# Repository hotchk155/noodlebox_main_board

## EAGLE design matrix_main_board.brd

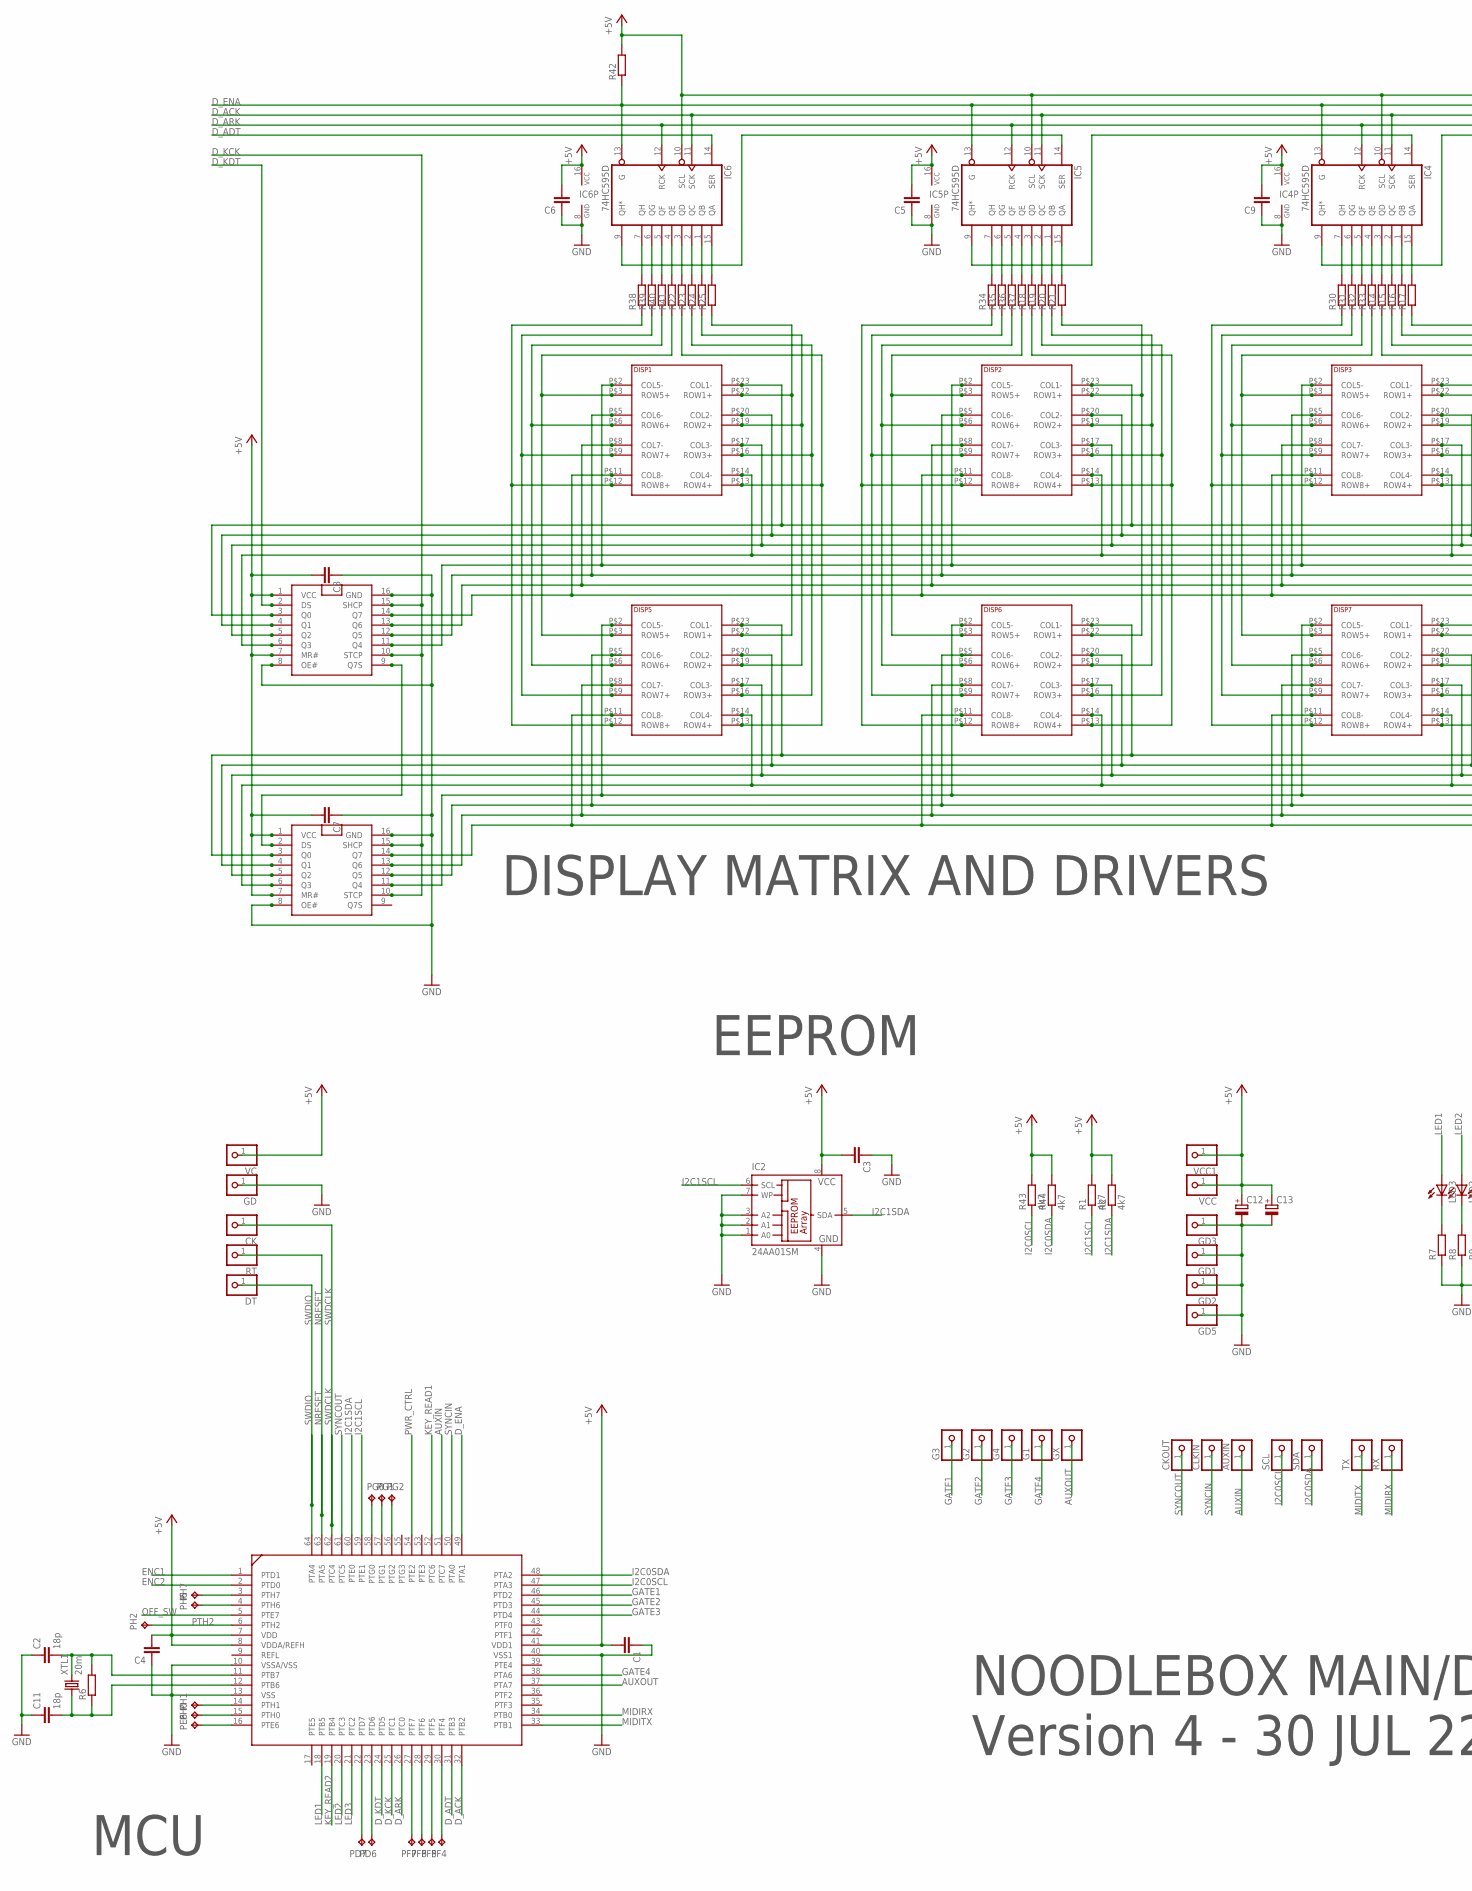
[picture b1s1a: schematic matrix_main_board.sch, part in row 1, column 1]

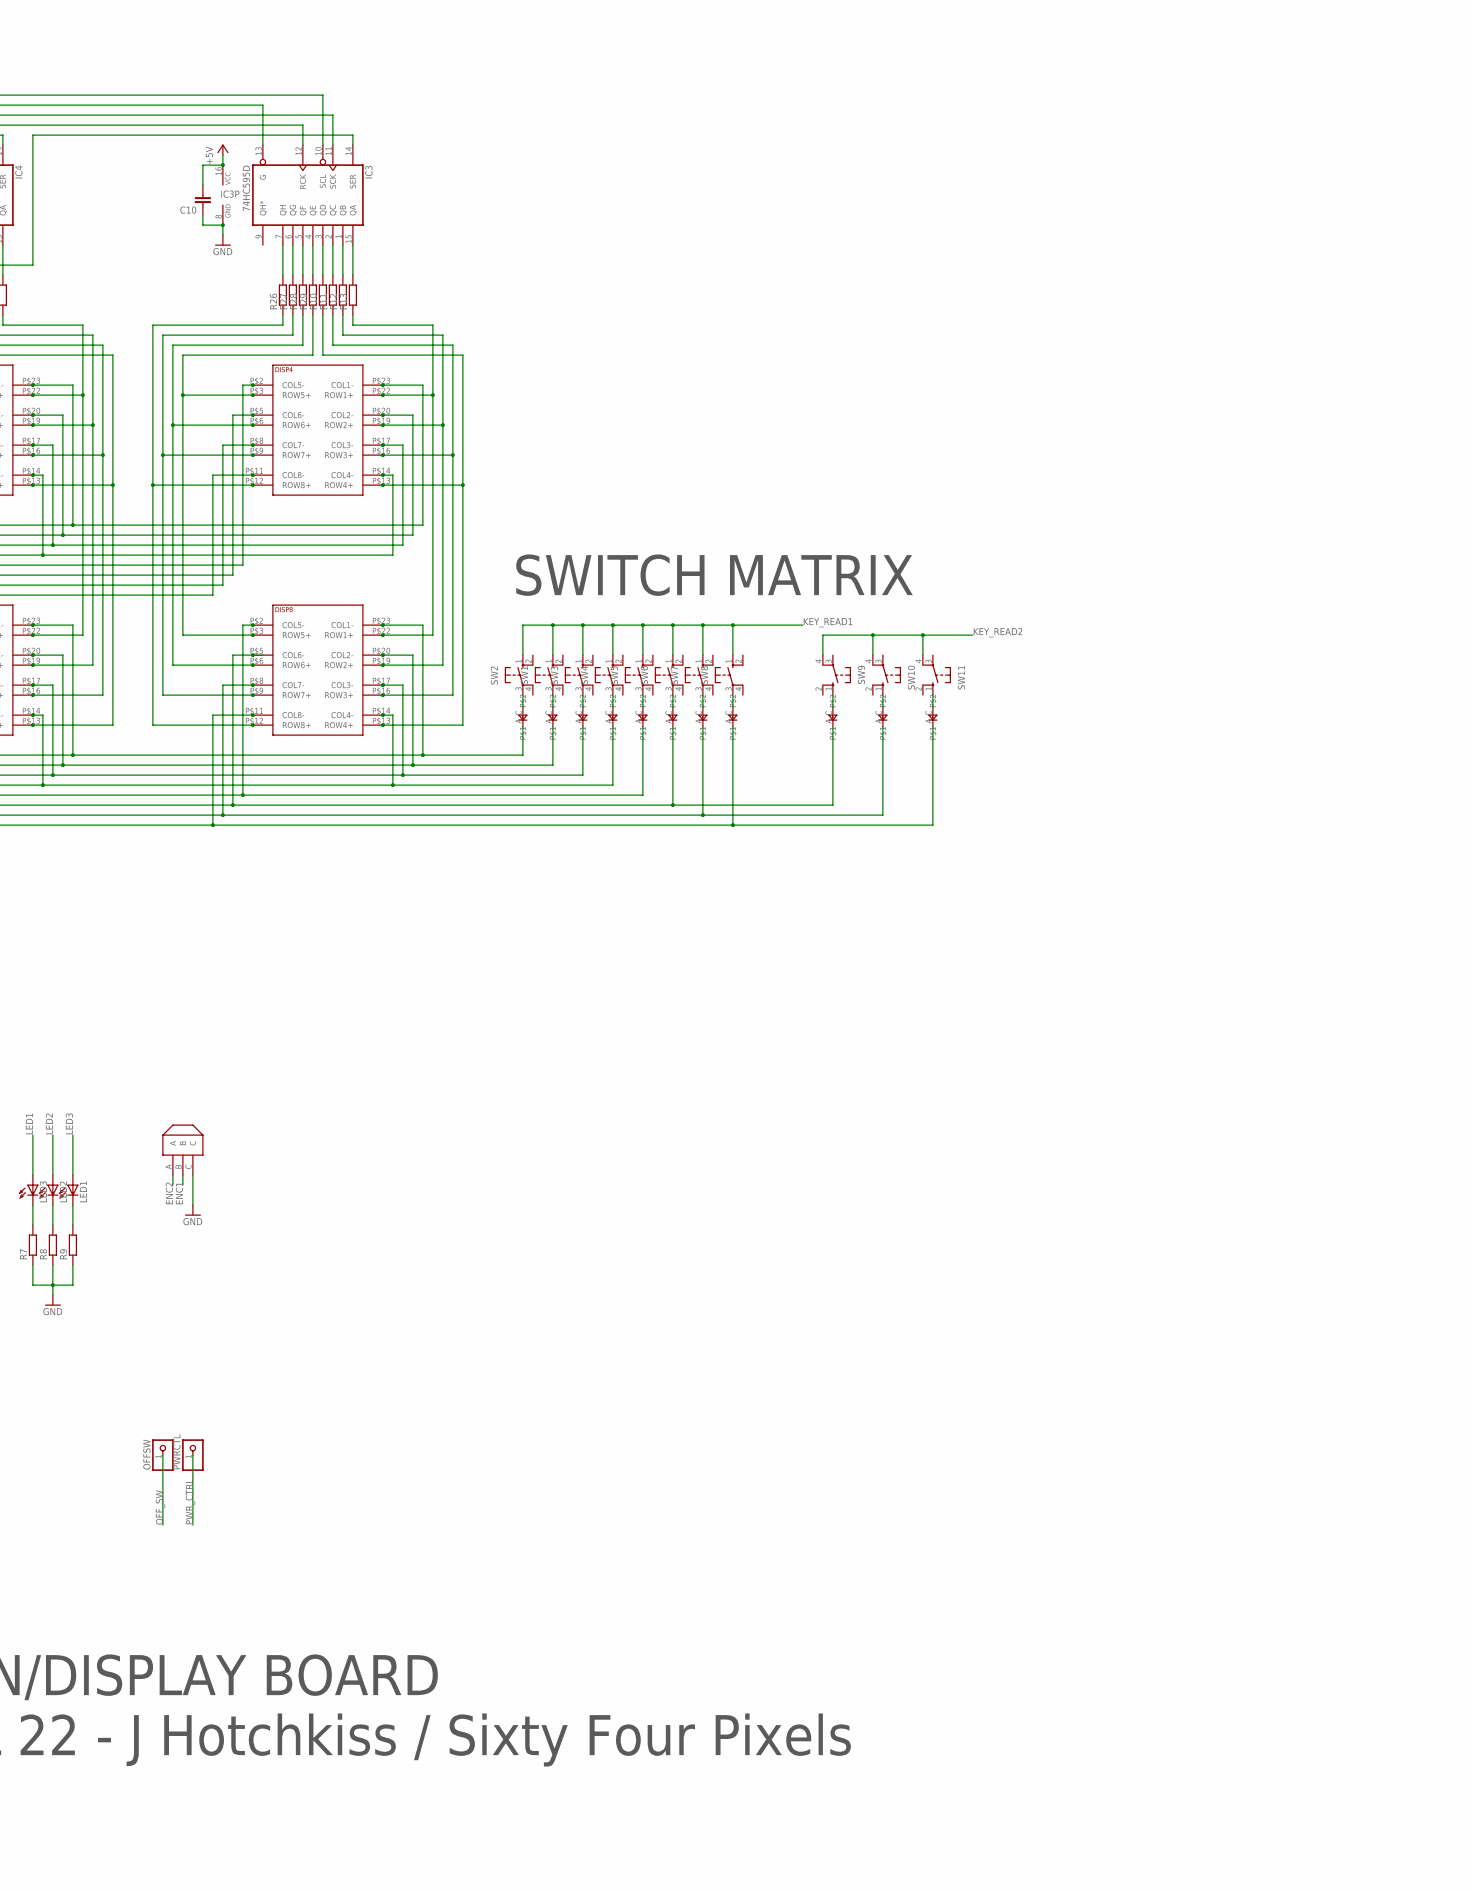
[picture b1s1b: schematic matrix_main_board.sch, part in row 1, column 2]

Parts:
AUXIN: PINHD-1X1; 1X01
C1, C3, C4, C5, C6, C7, C8, C9, C10: C-EUC0805; C0805
C2, C11: 18p; C0805
C12, C13: CPOL-EUE2.5-7; E2,5-7
CK: PINHD-1X1; 1X01
CKOUT: PINHD-1X1; 1X01
CLKIN: PINHD-1X1; 1X01
D1, D2, D3, D4, D5, D6, D7, D8, D9, D10, D11: 0805DIODE
DISP1, DISP2, DISP3, DISP4, DISP5, DISP6, DISP7, DISP8: 1388BBMATRIX24PIN; 1388_24PIN
DT: PINHD-1X1; 1X01
ENC1: ENCODER
G1, G2, G3, G4: PINHD-1X1; 1X01
GD, GD1, GD2, GD3, GD5: PINHD-1X1; 1X01
GX: PINHD-1X1; 1X01
IC1: MKE02_64PINQFP64; QFP64_SOT393
IC2: 24AA01SM; SO-08M
IC3, IC4, IC5, IC6: 74HC595D; SO16
IC7, IC8: NPIC6C596; SO16
LED1, LED2, LED3: LED3MM
OFFSW: PINHD-1X1; 1X01
PD6, PD7: TPTP17R; TP17R
PE6: TPTP17R; TP17R
PF4, PF5, PF6, PF7: TPTP17R; TP17R
PG0, PG1, PG2: TPTP17R; TP17R
PH0, PH1, PH2, PH6, PH7: TPTP17R; TP17R
PWRCTL: PINHD-1X1; 1X01
R1, R2, R43, R44: 4k7; R0805
R6, R7, R8, R9, R10, R11, R12, R13, R14, R15, R16, R17, R18, R19, R20, R21, R22, R23, R24, R25, R26, R27, R28, R29, R30, R31, R32, R33, R34, R35, R36, R37, R38, R39, R40, R41, R42: R-EU_R0805; R0805
RT: PINHD-1X1; 1X01
RX: PINHD-1X1; 1X01
SCL: PINHD-1X1; 1X01
SDA: PINHD-1X1; 1X01
SW1, SW2, SW3, SW4, SW5, SW6, SW7, SW8: 40-XX; B3F-40XX
SW9, SW10, SW11: 10-XX; B3F-10XX
TX: PINHD-1X1; 1X01
VC: PINHD-1X1; 1X01
VCC, VCC1: PINHD-1X1; 1X01
XTL1: 20m; HC49/S

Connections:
+5V: C1.2, C3.2, C4.2, C5.2, C6.2, C7.2, C8.2, C9.2, C10.2, C12.+, C13.+, IC1.7 (VDD), IC1.8 (VDDA/REFH), IC1.41 (VDD1), IC2.8 (VCC), IC3.10 (SCL), IC3.16 (VCC), IC4.10 (SCL), IC4.16 (VCC), IC5.10 (SCL), IC5.16 (VCC), IC6.10 (SCL), IC6.16 (VCC), IC7.1 (VCC), IC7.7 (MR#), IC8.1 (VCC), IC8.7 (MR#), R1.2, R2.2, R42.2, R43.2, R44.2, VC.1, VCC.1, VCC1.1
A0: DISP1.P$22 (ROW1+), DISP5.P$22 (ROW1+), R25.1
A1: DISP1.P$19 (ROW2+), DISP5.P$19 (ROW2+), R24.1
A2: DISP1.P$16 (ROW3+), DISP5.P$16 (ROW3+), R23.1
A3: DISP1.P$13 (ROW4+), DISP5.P$13 (ROW4+), R22.1
A4: DISP1.P$3 (ROW5+), DISP5.P$3 (ROW5+), R41.1
A5: DISP1.P$6 (ROW6+), DISP5.P$6 (ROW6+), R40.1
A6: DISP1.P$9 (ROW7+), DISP5.P$9 (ROW7+), R39.1
A7: DISP1.P$12 (ROW8+), DISP5.P$12 (ROW8+), R38.1
A8: DISP2.P$22 (ROW1+), DISP6.P$22 (ROW1+), R21.1
A9: DISP2.P$19 (ROW2+), DISP6.P$19 (ROW2+), R20.1
A10: DISP2.P$16 (ROW3+), DISP6.P$16 (ROW3+), R19.1
A11: DISP2.P$13 (ROW4+), DISP6.P$13 (ROW4+), R18.1
A12: DISP2.P$3 (ROW5+), DISP6.P$3 (ROW5+), R37.1
A13: DISP2.P$6 (ROW6+), DISP6.P$6 (ROW6+), R36.1
A14: DISP2.P$9 (ROW7+), DISP6.P$9 (ROW7+), R35.1
A15: DISP2.P$12 (ROW8+), DISP6.P$12 (ROW8+), R34.1
A16: DISP3.P$22 (ROW1+), DISP7.P$22 (ROW1+), R17.1
A17: DISP3.P$19 (ROW2+), DISP7.P$19 (ROW2+), R16.1
A18: DISP3.P$16 (ROW3+), DISP7.P$16 (ROW3+), R15.1
A19: DISP3.P$13 (ROW4+), DISP7.P$13 (ROW4+), R14.1
A20: DISP3.P$3 (ROW5+), DISP7.P$3 (ROW5+), R33.1
A21: DISP3.P$6 (ROW6+), DISP7.P$6 (ROW6+), R32.1
A22: DISP3.P$9 (ROW7+), DISP7.P$9 (ROW7+), R31.1
A23: DISP3.P$12 (ROW8+), DISP7.P$12 (ROW8+), R30.1
A24: DISP4.P$22 (ROW1+), DISP8.P$22 (ROW1+), R13.1
A25: DISP4.P$19 (ROW2+), DISP8.P$19 (ROW2+), R12.1
A26: DISP4.P$16 (ROW3+), DISP8.P$16 (ROW3+), R11.1
A27: DISP4.P$13 (ROW4+), DISP8.P$13 (ROW4+), R10.1
A28: DISP4.P$3 (ROW5+), DISP8.P$3 (ROW5+), R29.1
A29: DISP4.P$6 (ROW6+), DISP8.P$6 (ROW6+), R28.1
A30: DISP4.P$9 (ROW7+), DISP8.P$9 (ROW7+), R27.1
A31: DISP4.P$12 (ROW8+), DISP8.P$12 (ROW8+), R26.1
AUXIN: AUXIN.1, IC1.51 (PTC7)
AUXOUT: GX.1, IC1.37 (PTA7)
D_ACK: IC1.32 (PTB2), IC3.11 (SCK), IC4.11 (SCK), IC5.11 (SCK), IC6.11 (SCK)
D_ADT: IC1.31 (PTB3), IC6.14 (SER)
D_ARK: IC1.26 (PTC0), IC3.12 (RCK), IC4.12 (RCK), IC5.12 (RCK), IC6.12 (RCK)
D_ENA: IC1.49 (PTA1), IC3.13 (G), IC4.13 (G), IC5.13 (G), IC6.13 (G), R42.1
D_KCK: IC1.25 (PTC1), IC7.10 (STCP), IC7.15 (SHCP), IC8.10 (STCP), IC8.15 (SHCP)
D_KDT: IC1.24 (PTD5), IC8.2 (DS)
ENC1: ENC1.B, IC1.1 (PTD1)
ENC2: ENC1.A, IC1.2 (PTD0)
GATE1: G3.1, IC1.46 (PTD2)
GATE2: G2.1, IC1.45 (PTD3)
GATE3: G4.1, IC1.44 (PTD4)
GATE4: G1.1, IC1.38 (PTA6)
GND: C1.1, C2.1, C3.1, C4.1, C5.1, C6.1, C7.1, C8.1, C9.1, C10.1, C11.1, C12.-, C13.-, ENC1.C, GD.1, GD1.1, GD2.1, GD3.1, GD5.1, IC1.10 (VSSA/VSS), IC1.13 (VSS), IC1.40 (VSS1), IC2.1 (A0), IC2.2 (A1), IC2.3 (A2), IC2.4 (GND), IC2.7 (WP), IC3.8 (GND), IC4.8 (GND), IC5.8 (GND), IC6.8 (GND), IC7.8 (OE#), IC7.16 (GND), IC8.8 (OE#), IC8.16 (GND), R7.1, R8.1, R9.1
I2C0SCL: IC1.47 (PTA3), R43.1, SCL.1
I2C0SDA: IC1.48 (PTA2), R44.1, SDA.1
I2C1SCL: IC1.59 (PTE1), IC2.6 (SCL), R1.1
I2C1SDA: IC1.60 (PTE0), IC2.5 (SDA), R2.1
K0: DISP1.P$23 (COL1-), DISP2.P$23 (COL1-), DISP3.P$23 (COL1-), DISP4.P$23 (COL1-), IC8.3 (Q0)
K1: DISP1.P$20 (COL2-), DISP2.P$20 (COL2-), DISP3.P$20 (COL2-), DISP4.P$20 (COL2-), IC8.4 (Q1)
K2: DISP1.P$17 (COL3-), DISP2.P$17 (COL3-), DISP3.P$17 (COL3-), DISP4.P$17 (COL3-), IC8.5 (Q2)
K3: DISP1.P$14 (COL4-), DISP2.P$14 (COL4-), DISP3.P$14 (COL4-), DISP4.P$14 (COL4-), IC8.6 (Q3)
K4: DISP1.P$2 (COL5-), DISP2.P$2 (COL5-), DISP3.P$2 (COL5-), DISP4.P$2 (COL5-), IC8.11 (Q4)
K5: DISP1.P$5 (COL6-), DISP2.P$5 (COL6-), DISP3.P$5 (COL6-), DISP4.P$5 (COL6-), IC8.12 (Q5)
K6: DISP1.P$8 (COL7-), DISP2.P$8 (COL7-), DISP3.P$8 (COL7-), DISP4.P$8 (COL7-), IC8.13 (Q6)
K7: DISP1.P$11 (COL8-), DISP2.P$11 (COL8-), DISP3.P$11 (COL8-), DISP4.P$11 (COL8-), IC8.14 (Q7)
K8: D7.A, DISP5.P$23 (COL1-), DISP6.P$23 (COL1-), DISP7.P$23 (COL1-), DISP8.P$23 (COL1-), IC7.3 (Q0)
K9: D8.A, DISP5.P$20 (COL2-), DISP6.P$20 (COL2-), DISP7.P$20 (COL2-), DISP8.P$20 (COL2-), IC7.4 (Q1)
K10: D6.A, DISP5.P$17 (COL3-), DISP6.P$17 (COL3-), DISP7.P$17 (COL3-), DISP8.P$17 (COL3-), IC7.5 (Q2)
K11: D5.A, DISP5.P$14 (COL4-), DISP6.P$14 (COL4-), DISP7.P$14 (COL4-), DISP8.P$14 (COL4-), IC7.6 (Q3)
K12: D4.A, DISP5.P$2 (COL5-), DISP6.P$2 (COL5-), DISP7.P$2 (COL5-), DISP8.P$2 (COL5-), IC7.11 (Q4)
K13: D3.A, D11.A, DISP5.P$5 (COL6-), DISP6.P$5 (COL6-), DISP7.P$5 (COL6-), DISP8.P$5 (COL6-), IC7.12 (Q5)
K14: D2.A, D10.A, DISP5.P$8 (COL7-), DISP6.P$8 (COL7-), DISP7.P$8 (COL7-), DISP8.P$8 (COL7-), IC7.13 (Q6)
K15: D1.A, D9.A, DISP5.P$11 (COL8-), DISP6.P$11 (COL8-), DISP7.P$11 (COL8-), DISP8.P$11 (COL8-), IC7.14 (Q7)
KEY_READ1: IC1.52 (PTC6), SW1.1 (S), SW2.1 (S), SW3.1 (S), SW4.1 (S), SW5.1 (S), SW6.1 (S), SW7.1 (S), SW8.1 (S)
KEY_READ2: IC1.19 (PTB4), SW9.4 (P1), SW10.4 (P1), SW11.4 (P1)
LED1: IC1.18 (PTB5), LED3.A
LED2: IC1.20 (PTC3), LED2.A
LED3: IC1.21 (PTC2), LED1.A
MIDIRX: IC1.34 (PTB0), RX.1
MIDITX: IC1.33 (PTB1), TX.1
unnamed: D10.C, SW10.1 (S)
unnamed: LED3.K (C), R7.2
unnamed: LED2.K (C), R8.2
unnamed: C2.2, IC1.11 (PTB7), R6.2, XTL1.2
unnamed: C11.2, IC1.12 (PTB6), R6.1, XTL1.1
unnamed: LED1.K (C), R9.2
unnamed: D9.C, SW11.1 (S)
unnamed: D11.C, SW9.1 (S)
unnamed: D7.C, SW2.3
unnamed: IC1.22 (PTD7), PD7.TP
unnamed: D8.C, SW1.3
unnamed: IC1.23 (PTD6), PD6.TP
unnamed: D6.C, SW3.3
unnamed: D5.C, SW4.3
unnamed: IC1.27 (PTF7), PF7.TP
unnamed: D4.C, SW5.3
unnamed: IC6.15 (QA), R25.2
unnamed: IC6.1 (QB), R24.2
unnamed: IC6.2 (QC), R23.2
unnamed: IC6.3 (QD), R22.2
unnamed: IC6.4 (QE), R41.2
unnamed: IC6.5 (QF), R40.2
unnamed: IC6.6 (QG), R39.2
unnamed: IC6.7 (QH), R38.2
unnamed: IC1.28 (PTF6), PF6.TP
unnamed: IC1.29 (PTF5), PF5.TP
unnamed: IC1.30 (PTF4), PF4.TP
unnamed: IC5.14 (SER), IC6.9 (QH*)
unnamed: IC4.14 (SER), IC5.9 (QH*)
unnamed: IC3.14 (SER), IC4.9 (QH*)
unnamed: IC1.14 (PTH1), PH1.TP
unnamed: IC1.15 (PTH0), PH0.TP
unnamed: IC1.16 (PTE6), PE6.TP
unnamed: IC1.4 (PTH6), PH6.TP
unnamed: IC1.57 (PTG1), PG1.TP
unnamed: IC5.15 (QA), R21.2
unnamed: IC5.1 (QB), R20.2
unnamed: IC5.2 (QC), R19.2
unnamed: IC5.3 (QD), R18.2
unnamed: IC5.4 (QE), R37.2
unnamed: IC5.5 (QF), R36.2
unnamed: IC5.6 (QG), R35.2
unnamed: IC5.7 (QH), R34.2
unnamed: D3.C, SW6.3
unnamed: D2.C, SW7.3
unnamed: D1.C, SW8.3
unnamed: IC4.15 (QA), R17.2
unnamed: IC4.1 (QB), R16.2
unnamed: IC4.2 (QC), R15.2
unnamed: IC4.3 (QD), R14.2
unnamed: IC4.4 (QE), R33.2
unnamed: IC4.5 (QF), R32.2
unnamed: IC4.6 (QG), R31.2
unnamed: IC4.7 (QH), R30.2
unnamed: IC3.15 (QA), R13.2
unnamed: IC3.1 (QB), R12.2
unnamed: IC3.2 (QC), R11.2
unnamed: IC3.3 (QD), R10.2
unnamed: IC3.4 (QE), R29.2
unnamed: IC3.5 (QF), R28.2
unnamed: IC3.6 (QG), R27.2
unnamed: IC3.7 (QH), R26.2
unnamed: IC7.2 (DS), IC8.9 (Q7S)
NRESET: IC1.63 (PTA5), RT.1
OFF_SW: IC1.5 (PTE7), OFFSW.1
PG0: IC1.58 (PTG0), PG0.TP
PTG2: IC1.56 (PTG2), PG2.TP
PTH2: IC1.6 (PTH2), PH2.TP
PTH7: IC1.3 (PTH7), PH7.TP
PWR_CTRL: IC1.54 (PTE2), PWRCTL.1
SWDCLK: CK.1, IC1.62 (PTC4)
SWDIO: DT.1, IC1.64 (PTA4)
SYNCIN: CLKIN.1, IC1.50 (PTA0)
SYNCOUT: CKOUT.1, IC1.61 (PTC5)

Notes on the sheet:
DISPLAY MATRIX AND DRIVERS
SWITCH MATRIX
MCU
EEPROM
NOODLEBOX MAIN/DISPLAY BOARD
Version 4 - 30 JUL 22 - J Hotchkiss / Sixty Four Pixels

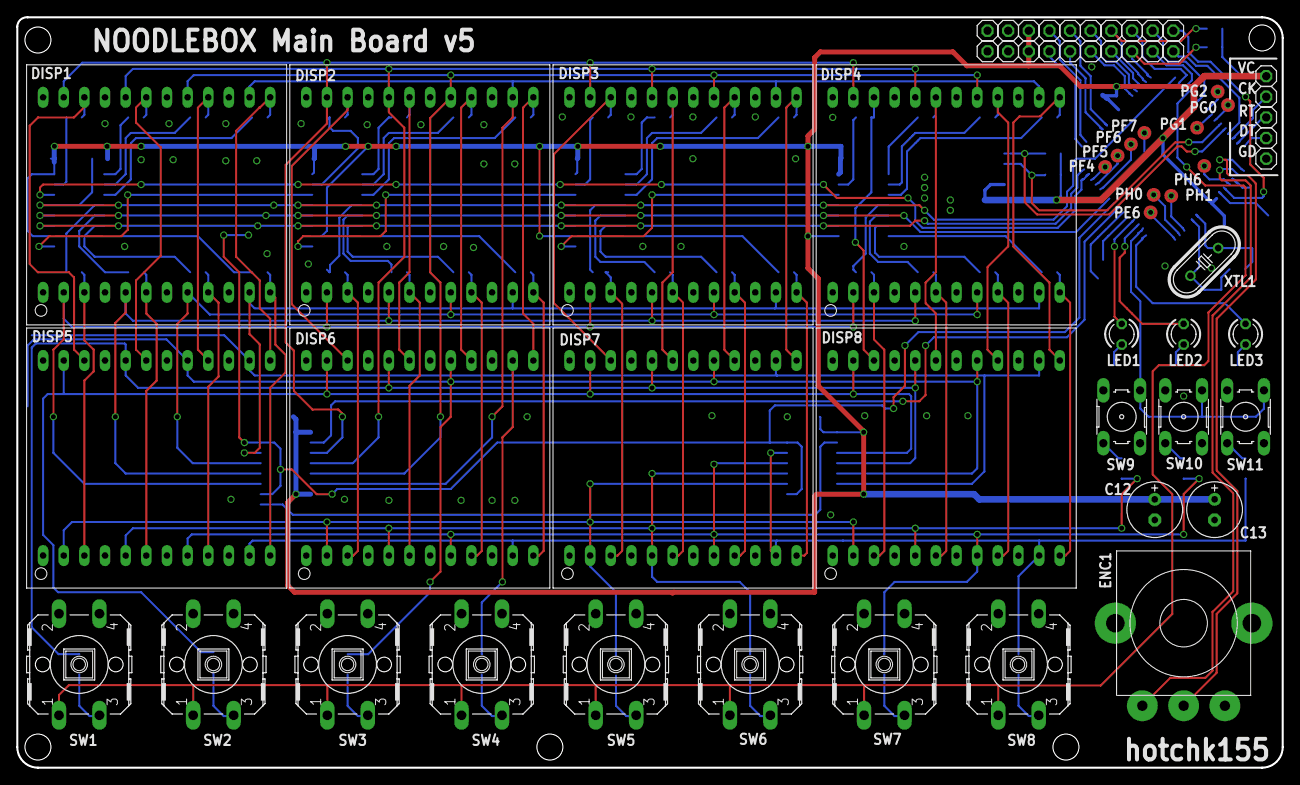
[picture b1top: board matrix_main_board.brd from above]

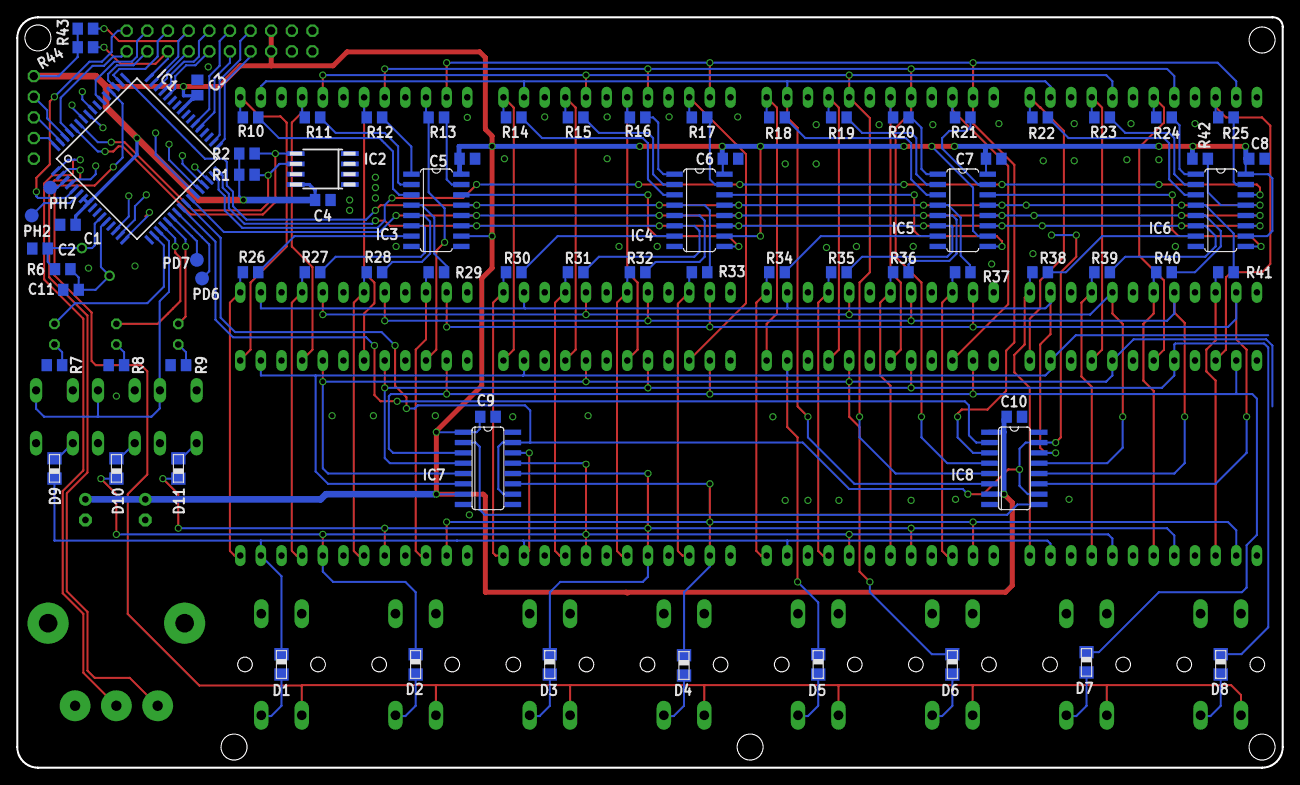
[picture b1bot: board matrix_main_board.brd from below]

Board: 2 copper layers, 155.7 x 92.3 mm, 137 parts (75 on the bottom side), 149 nets.

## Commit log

2018-07-10 VERSION 1
2019-05-19 values
2019-05-19 changes for rev2
2019-11-26 works in progress
2019-11-26 V3 candidate
2022-04-12 dsfdfs
2022-04-14 ASAS
2022-04-22 3v3/rp2010
2022-07-30 Rolling back RP2040 changes
2022-07-30 in prog
2022-07-31 work in prog
2022-08-03 64pin
2022-11-24 correct footprint
2022-11-24 V5 BOARD
